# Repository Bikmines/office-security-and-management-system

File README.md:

# office-security-and-management-system
office security and management system -> my final year project

final1 is arduino program for MFRC522,keypad,SD card sheild

Final1.ino is program for password based entry and user attendence system using RF cards and tags and storing them in SD card

BIDIR.ino is for bidirection visitor counter and displaying them on LCD. Along with DHT11 sensor which senses the temperature of surrounding and triggers alarm when temperature exceeds the limit given in case of fire hazards.
ir2 is PCB design designed using eagle

IRledcontrol.ino is program to control the AC bulb with any remote. Also it contains the motor with camera which is constantly monitoring the office as one gets into restricted area the motor rotates and focuses camera in that directio
ir1 is the PCB design designed using eagle

:-)   :-)     :-)     :-)     :-)             :-)                             :-)                                         :-)

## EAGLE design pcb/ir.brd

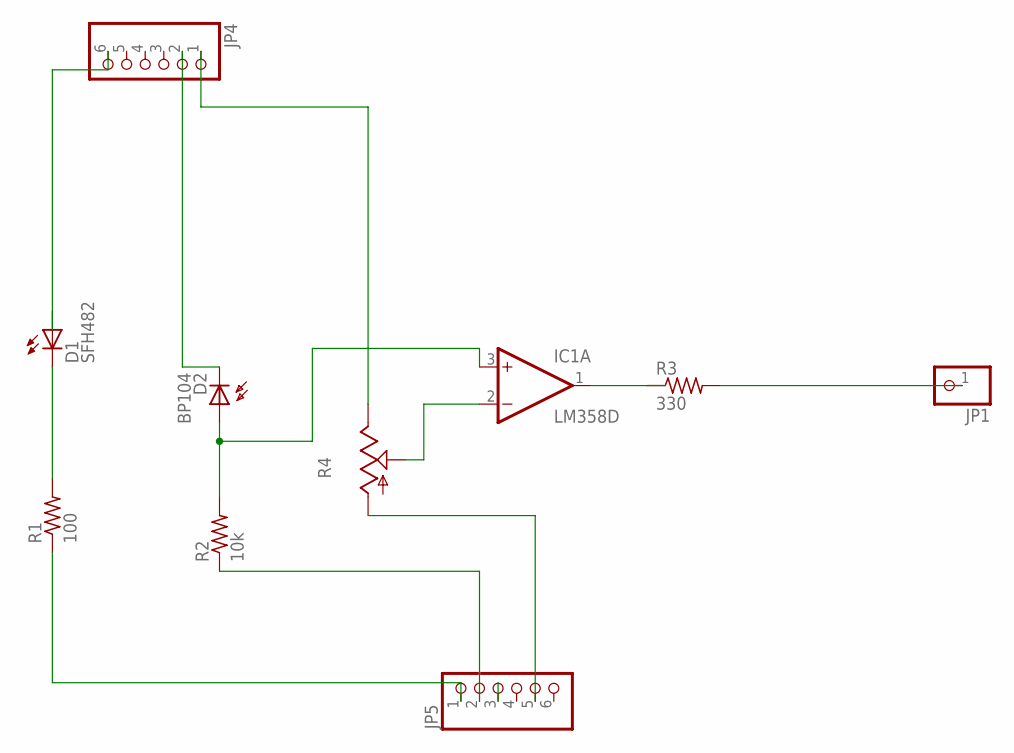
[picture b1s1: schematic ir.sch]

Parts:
D1: SFH482
D2: BP104
IC1: LM358D; SO08
JP1: PINHD-1X1; 1X01
JP4, JP5: PINHD-1X6; 1X06
R1: 100; 0204/7
R2: 10k; 0204/7
R3: 330; 0204/7
R4: TRIM_US-3223G; 3223G

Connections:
unnamed: D2.K (C), JP4.2
unnamed: D1.K (C), R1.2
unnamed: JP5.1, R1.1
unnamed: D2.A, IC1.3 (+IN), R2.2
unnamed: JP5.5, R4.1 (A)
unnamed: IC1.1 (OUT), R3.1
unnamed: JP1.1, R3.2
unnamed: D1.A, JP4.6
unnamed: JP4.1, R4.3 (E)
unnamed: IC1.2 (-IN), R4.2 (S)
unnamed: JP5.2, R2.1
V+: IC1.8 (V+)
V-: IC1.4 (V-)

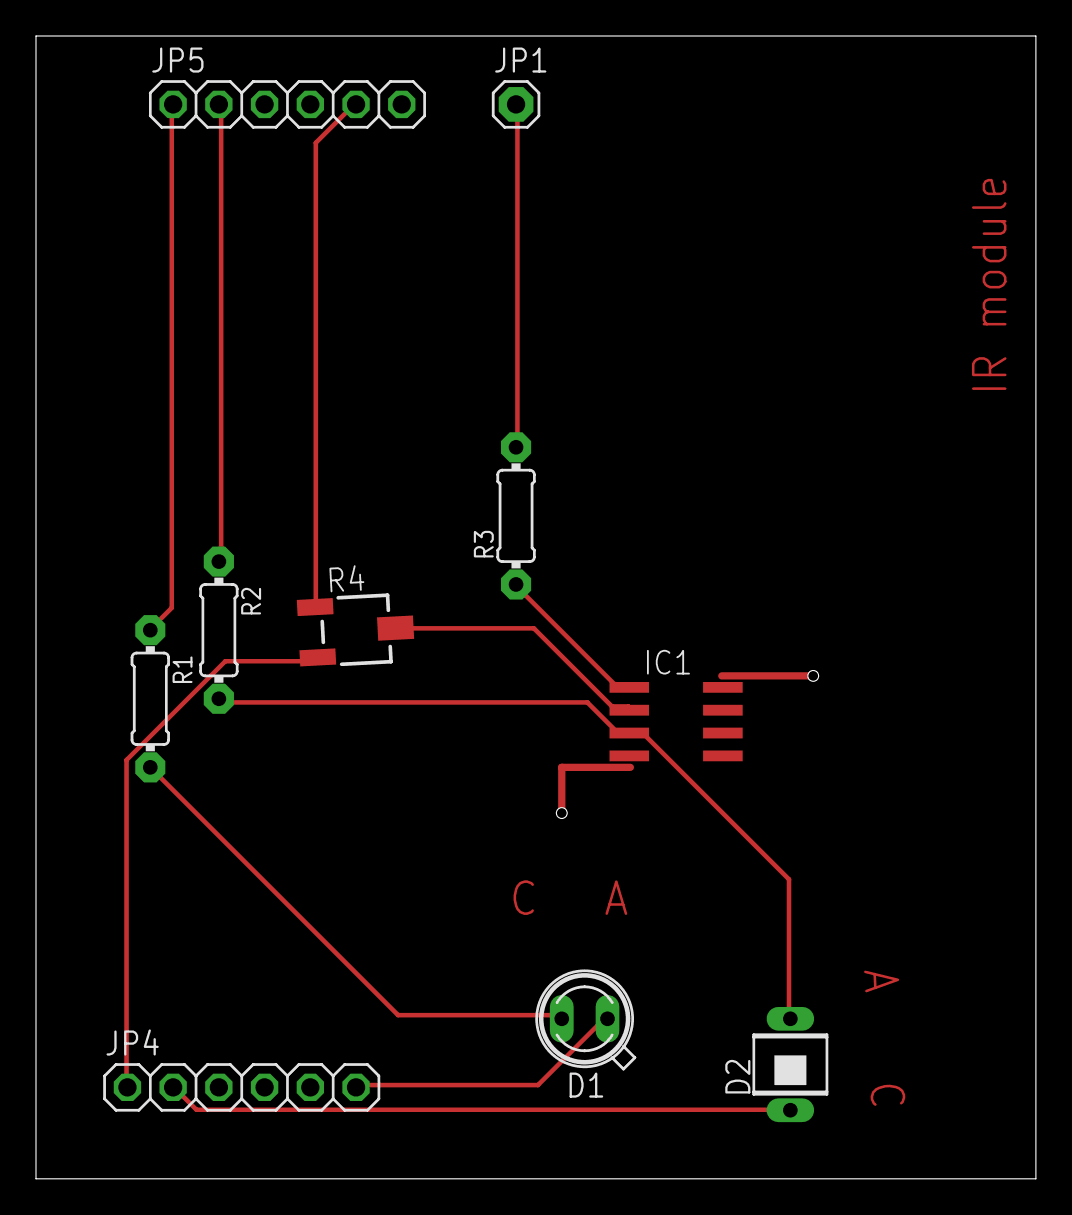
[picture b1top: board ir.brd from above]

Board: 2 copper layers, 55.5 x 63.5 mm, 10 parts (0 on the bottom side), 11 nets.
